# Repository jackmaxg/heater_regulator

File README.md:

# heater_regulator
A simple comparator based controller for temperature regulating a resistive heater

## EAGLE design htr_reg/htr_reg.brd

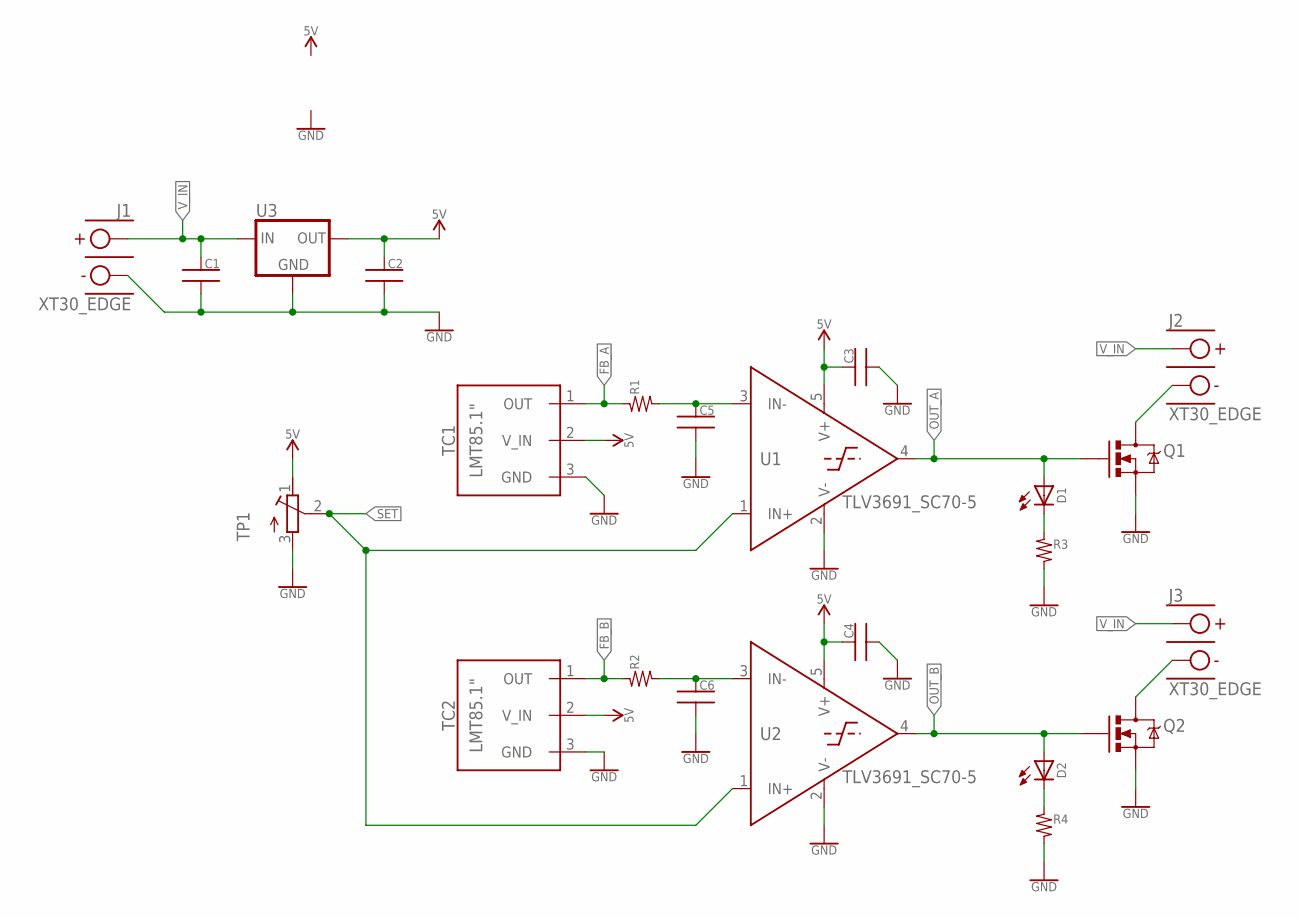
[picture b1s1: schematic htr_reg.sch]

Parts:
C1, C2, C3, C4, C5, C6: CAP_SMD_0603; 0603
D1, D2: LED0603; LED-0603
J1, J2, J3: XT30_EDGE; XT30_EDGEMOUNT
Q1, Q2: MOSFET_N-CHANNEL_SOT23-3; SOT23-3
R1, R2, R3, R4: RES_SMD0603; 0603
TC1, TC2: LMT85.1"; 1X03
TP1: 3296W
U1, U2: TLV3691_SC70-5; SC70-5
U3: 78XX_VREG_B; SOT23-3

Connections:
5V: C2.1, C3.1, C4.1, TC1.2 (V_IN), TC2.2 (V_IN), TP1.1 (E), U1.5 (V+), U2.5 (V+), U3.2 (OUT)
FB_A: R1.1, TC1.1 (OUT)
FB_B: R2.1, TC2.1 (OUT)
GND: C1.2, C2.2, C3.2, C4.2, C5.2, C6.2, J1.NEG, Q1.2 (S), Q2.2 (S), R3.2, R4.2, TC1.3 (GND), TC2.3 (GND), TP1.3 (A), U1.2 (V-), U2.2 (V-), U3.1 (GND)
unnamed: D1.C, R3.1
unnamed: D2.C, R4.1
unnamed: J3.NEG, Q2.3 (D)
unnamed: J2.NEG, Q1.3 (D)
unnamed: C6.1, R2.2, U2.3 (IN-)
unnamed: C5.1, R1.2, U1.3 (IN-)
OUT_A: D1.A, Q1.1 (G), U1.4 (OUT)
OUT_B: D2.A, Q2.1 (G), U2.4 (OUT)
SET: TP1.2 (S), U1.1 (IN+), U2.1 (IN+)
V_IN: C1.1, J1.POS, J2.POS, J3.POS, U3.3 (IN)

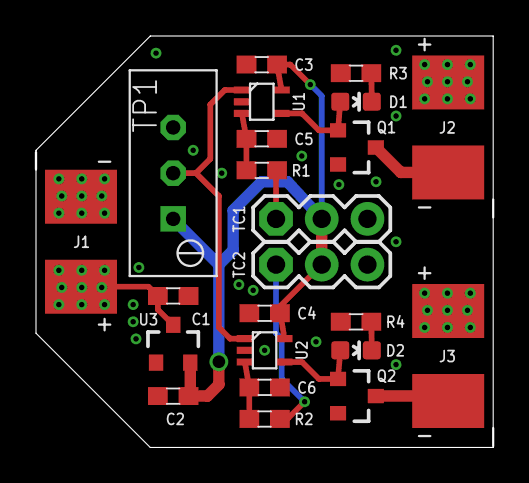
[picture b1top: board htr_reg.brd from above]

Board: 2 copper layers, 25.4 x 22.9 mm, 23 parts (0 on the bottom side), 14 nets.

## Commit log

2018-06-21 added the gitattributes and ignore files
2018-06-21 Made an empty sch file and project. Created a library and started adding important parts to it
2018-06-21 added a few more bits to the library, started assembling the schematic, brd file created.
2018-06-21 organized and connected the schematic
2018-06-22 Added and twiddled small bits of the lib. Routed traces on the board, possibly finished.
2018-07-13 Probably layed out the board and generated gerbers for it
